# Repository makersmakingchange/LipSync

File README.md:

# LipSync

The LipSync is a mouth-operated sip-and-puff joystick that can emulate a mouse, wireless Bluetooth mouse, or gamepad. It enables people with disabilities that limit their mobility to control a computer, gaming console, smart phone, or tablet.

This most recent version, the LipSync 4.1, is made up of the LipSync Joystick and LipSync Hub. The Joystick is the primary user interface, and contains a low-force Hall-Effect joystick and sip and puff sensors. The Hub has a display that provides a graphical interface for independently adjusting settings, as well as it provides the connection to the host device and up to three external assistive switches with 3.5 mm jacks.

The device is comprised of off-the-shelf electronics and hardware, a custom PCB and 3D printed parts. The overall cost of materials (including materials required in bulk) for a single build is about $325 (plus shipping). In larger quantities, the cost of materials is closer to $175.

The LipSync is compatible with a range of host devices that are able to support a USB Mouse, a USB Gamepad and/or a Bluetooth Mouse. Compatible devices include PC and Mac computers and laptops, Android, iOS, and Windows smartphone and tablets, and the Xbox Adaptive Controller. 

The LipSync is Open Assistive Technology (OpenAT) and is certified as Open Source Hardware by the Open Source Hardware Association under the OSHWA UID [CA000046](https://certification.oshwa.org/ca000046.html). Under the terms of the open source hardware licenses, the LipSync may be built, used, and improved by anyone.  

Older versions of the LipSync are now obsolete. Documentation and design files are still available at the [LipSync Classic Repository.](https://github.com/makersmakingchange/OldLipSync)

The existing LipSync Interface Cable options in the BOM are not in stock. We are working on sourcing suitable alternatives.

Last updated: 2025-Jul-22

Makers Making Change Assistive Device Library Listing: [https://www.makersmakingchange.com/s/product/LipSync](https://www.makersmakingchange.com/s/product/lipsync/01tJR000000698fYAA)

## OpenAT Joysticks
This design is part of the [OpenAT Joystick Project](https://github.com/makersmakingchange/OpenAT-Joysticks), a collection of open source designs for digital access and adapted gaming. 

## How to Obtain the Device
### 1. Do-it-Yourself (DIY) or Do-it-Together (DIT)

This is an open-source assistive technology, so anyone is free to build it. All of the files and instructions required to build the device are contained within this repository. Refer to the Maker Guide below.

### 2. Request a build of this device

You may also submit a build request through the [MMC Library Page](https://www.makersmakingchange.com/s/product/LipSync/<mmc-salesforce-id>) to have a volunteer maker build the device. As the requestor, you are responsible for reimbursing the maker for the cost of materials and any shipping.

### 3. Build this device for someone else

If you have the skills and equipment to build this device, and would like to donate your time to create the device for someone who needs it, visit the [MMC Maker Wanted](https://makersmakingchange.com/maker-wanted/) section.

## Build Instructions

### 1. Read through the Maker Guide

The [Maker Guide](/Documentation/LipSync_Maker_Guide.pdf) contains all the necessary information to build this device, including tool lists, assembly instructions, programming instructions and testing instructions.

### 2. Order the Off-The-Shelf Components

The [Bill of Materials](/Documentation/LipSync_BOM.csv) lists all of the parts and components required to build the device. 

### 3. Print the 3D Printable components

All of the files and individual print files can be in the [/Build_Files/3D_Printing_Files](/Build_Files/3D_Printing_Files/) folder.

### 4. Assemble the LipSync

Reference the Assembly Guide section of the [Maker Guide](/Documentation/LipSync_Maker_Guide.pdf) for the tools and steps required to build each portion.

## How to improve this Device
As open source assistive technology, you are welcomed and encouraged to improve upon the design. 

## Files
### Documentation
| Document             | Version | Link                                                                     | Notes             |
|----------------------|---------|--------------------------------------------------------------------------|-------------------|
| Design Rationale     | 4.1     | [LipSync_Design_Rationale](/Documentation/LipSync_Design_Rationale.pdf)  |                   |
| Maker Guide          | 4.1     | [LipSync_Maker_Guide](/Documentation/LipSync_Maker_Guide.pdf)            |                   |
| Bill of Materials    | 4.1     | [LipSync_Bill_of_Materials](/Documentation/LipSync_BOM.csv)              |                   |
| User Guide           | 4.1     | [LipSync_User_Guide](/Documentation/LipSync_User_Guide.pdf)              |                   |
| Quickstart Guide     | 4.1     | [LipSync_Quickstart_Guide](/Documentation/LipSync_Quickstart_Guide.pdf)  |                   |
| Changelog            | 4.1     | [LipSync_Changelog](CHANGES.txt)                                         |                   |

### Design Files
 - [CAD Files](/Design_Files/CAD_Design_Files)
 - [PCB Files](/Design_Files/PCB_Design_Files)

### Build Files
 - [3D Printing Files](/Build_Files/3D_Printing_Files/)
 - [PCB Files](/Build_Files/PCB_Build_Files/)
 - [Firmware Files](/Build_Files/Firmware_Files)

## License
Copyright (c) 2024-2025 Neil Squire / Makers Making Change.

This repository describes Open Hardware:
 - Everything needed or used to design, make, test, or prepare the LipSync is licensed under the [CERN 2.0 Weakly Reciprocal license (CERN-OHL-W v2) or later](https://cern.ch/cern-ohl ) .
 - All software is under the [GNU General Public License v3.0 (GPL-3.0)](https://www.gnu.org/licenses/gpl.html).
 - Accompanying material such as instruction manuals, videos, and other copyrightable works that are useful but not necessary to design, make, test, or prepare the LipSync are published under a [Creative Commons Attribution-ShareAlike 4.0 license (CC BY-SA 4.0)](https://creativecommons.org/licenses/by-sa/4.0/) .

You may redistribute and modify this documentation and make products using it under the terms of the [CERN-OHL-W v2](https://cern.ch/cern-ohl).
This documentation is distributed WITHOUT ANY EXPRESS OR IMPLIED WARRANTY, INCLUDING OF MERCHANTABILITY, SATISFACTORY QUALITY AND FITNESS FOR A PARTICULAR PURPOSE.
Please see the CERN-OHL-W v2 for applicable conditions.

Source Location: https://github.com/makersmakingchange/LipSync

## Attribution

The LipSync was designed by Neil Squire Society / Makers Making Change. The initial development of a 3D printable LipSync was supported by the Google Impact Challenge: Disabilities grant from Google.org. Further development was supported through the Government of Canada's Innovation Science and Economic Development [Accessible Technology Program](https://ised-isde.canada.ca/site/accessible-technology-program). These and other funders have also enabled Neil Squire / Makers Making Change to deploy numerous LipSyncs to users at reduced cost.

The latest design (V4.0) incorporates feedback and suggestions from numerous users, clinicians, and volunteer makers. In particular, 4.0.AlphaII was tested by the following users: Omar Al-azawi, Don Danbrook, Ean Price, Jim Ryan and Kaileen Selig.

V4.0 incorporates several commercially available open source hardware components:
 - [Adafruit TLV493D Triple-Axis Magnetometer - STEMMA QT / Qwiic](https://www.adafruit.com/product/4366). The PCB design is available under a CC-BY-SA 3.0 license at https://github.com/adafruit/Adafruit-TLV493D-PCB. 
 - [Adafruit LPS33HW Water Resistant Pressure Sensor - STEMMA QT](https://www.adafruit.com/product/4414). The PCB design is available under a CC-BY-SA 3.0 license at https://github.com/adafruit/Adafruit-LPS3X-PCB. 
 - [Adafruit LPS22 Pressure Sensor - STEMMA QT / Qwiic - LPS22HB](https://www.adafruit.com/product/4633). The PCB design is available under a CC-BY-SA 3.0 license at https://github.com/adafruit/Adafruit-LPS2X-PCB. 
 - [Adafruit 128X64 monochrome OLED Display Board](https://www.adafruit.com/product/938). The PCB design is available under a CC-BY-SA 3.0 license at https://github.com/adafruit/Adafruit-128x64-Monochrome-OLED-PCB.
 - [SparkFun Qwiic Adapter Board (DEV-14495)](https://www.sparkfun.com/products/14495). The PCB design is available under a CC-BY-SA 4.0 license at https://github.com/sparkfun/Qwiic_Adapter.   
 - [SparkFun RJ11 Breakout Board (BOB-14021)](https://www.sparkfun.com/products/14021). The PCB design is available under a CC-BY-SA 3.0 license at https://github.com/sparkfun/RJ11_Breakout. 

The LipSync firmware utilizes the Arduino development platform, an open-source electronics platform based on easy-to-use hardware and software. Arduino is developed and maintained by the Arduino community, and the project wouldn't be possible without their contributions.
Arduino is a registered trademark of Arduino AG. For more information about Arduino and to contribute to the community, visit the official Arduino website at www.arduino.cc.
The LipSync Firmware code uses several libraries:
 - [Adafruit_BusIO](https://github.com/adafruit/Adafruit_BusIO)  by Adafruit
 - [Adafruit_GFX](https://github.com/adafruit/Adafruit-GFX-Library) by Adafruit
 - [Adafruit_LPS2X](https://github.com/adafruit/Adafruit_LPS2X) by Adafruit
 - [Adafruit_LPS33HW](https://github.com/adafruit/Adafruit_LPS35HW) by Adafruit
 - [Adafruit_Sensor](https://github.com/adafruit/Adafruit_Sensor) by Adafruit
 - [Adafruit_SSD1306](https://github.com/adafruit/Adafruit_SSD1306) by Adafruit
 - [ArduinoJson](https://github.com/bblanchon/ArduinoJson) by Benoit Blanchon
 - [TLV493D-A1B6](https://github.com/Infineon/TLV493D-A1B6-3DMagnetic-Sensor) by Infineon Technologies

### Contributors
Designers:
 
 - Derrick Andrews, Neil Squire Society / Makers Making Change.
 - Stephan Dobri, Neil Squire Society / Makers Making Change.
 - Tyler Fentie, Neil Squire Society / Makers Making Change.
 - Milad Hajihassan, Neil Squire Society / Makers Making Change.
 - Jake McIvor, Neil Squire Society / Makers Making Change.
 - Stephen Moyer, Neil Squire Society / Makers Making Change.
 - Brad Wellington, Neil Squire Society / Makers Making Change.
 - Josie Versloot, Neil Squire Society / Makers Making Change.
 
## Open Source Hardware Certification

The LipSync has been certified as open source hardware by the Open Source Hardware Association under the OSHWA UID [CA000046](https://certification.oshwa.org/ca000046.html).

---

<!-- ABOUT MMC START -->
## About Makers Making Change

Makers Making Change is a program of [Neil Squire](https://www.neilsquire.ca/), a Canadian non-profit that uses technology, knowledge, and passion to empower people with disabilities.

Makers Making Change leverages the capacity of community based Makers, Disability Professionals and Volunteers to develop and deliver affordable Open Source Assistive Technologies.

 - Website: [www.MakersMakingChange.com](https://www.makersmakingchange.com/)
 - GitHub: [makersmakingchange](https://github.com/makersmakingchange)
 - Bluesky: [@makersmakingchange.bsky.social](https://bsky.app/profile/makersmakingchange.bsky.social)
 - Instagram: [@makersmakingchange](https://www.instagram.com/makersmakingchange)
 - Facebook: [makersmakechange](https://www.facebook.com/makersmakechange)
 - LinkedIn: [Neil Squire Society](https://www.linkedin.com/company/neil-squire-society/)
 - Thingiverse: [makersmakingchange](https://www.thingiverse.com/makersmakingchange/about)
 - Printables: [MakersMakingChange](https://www.printables.com/@MakersMakingChange)

### Contact Us
For technical questions, to get involved, or to share your experience we encourage you to [visit our website](https://www.makersmakingchange.com/) or [contact us](https://www.makersmakingchange.com/s/contact).
<!-- ABOUT MMC END -->

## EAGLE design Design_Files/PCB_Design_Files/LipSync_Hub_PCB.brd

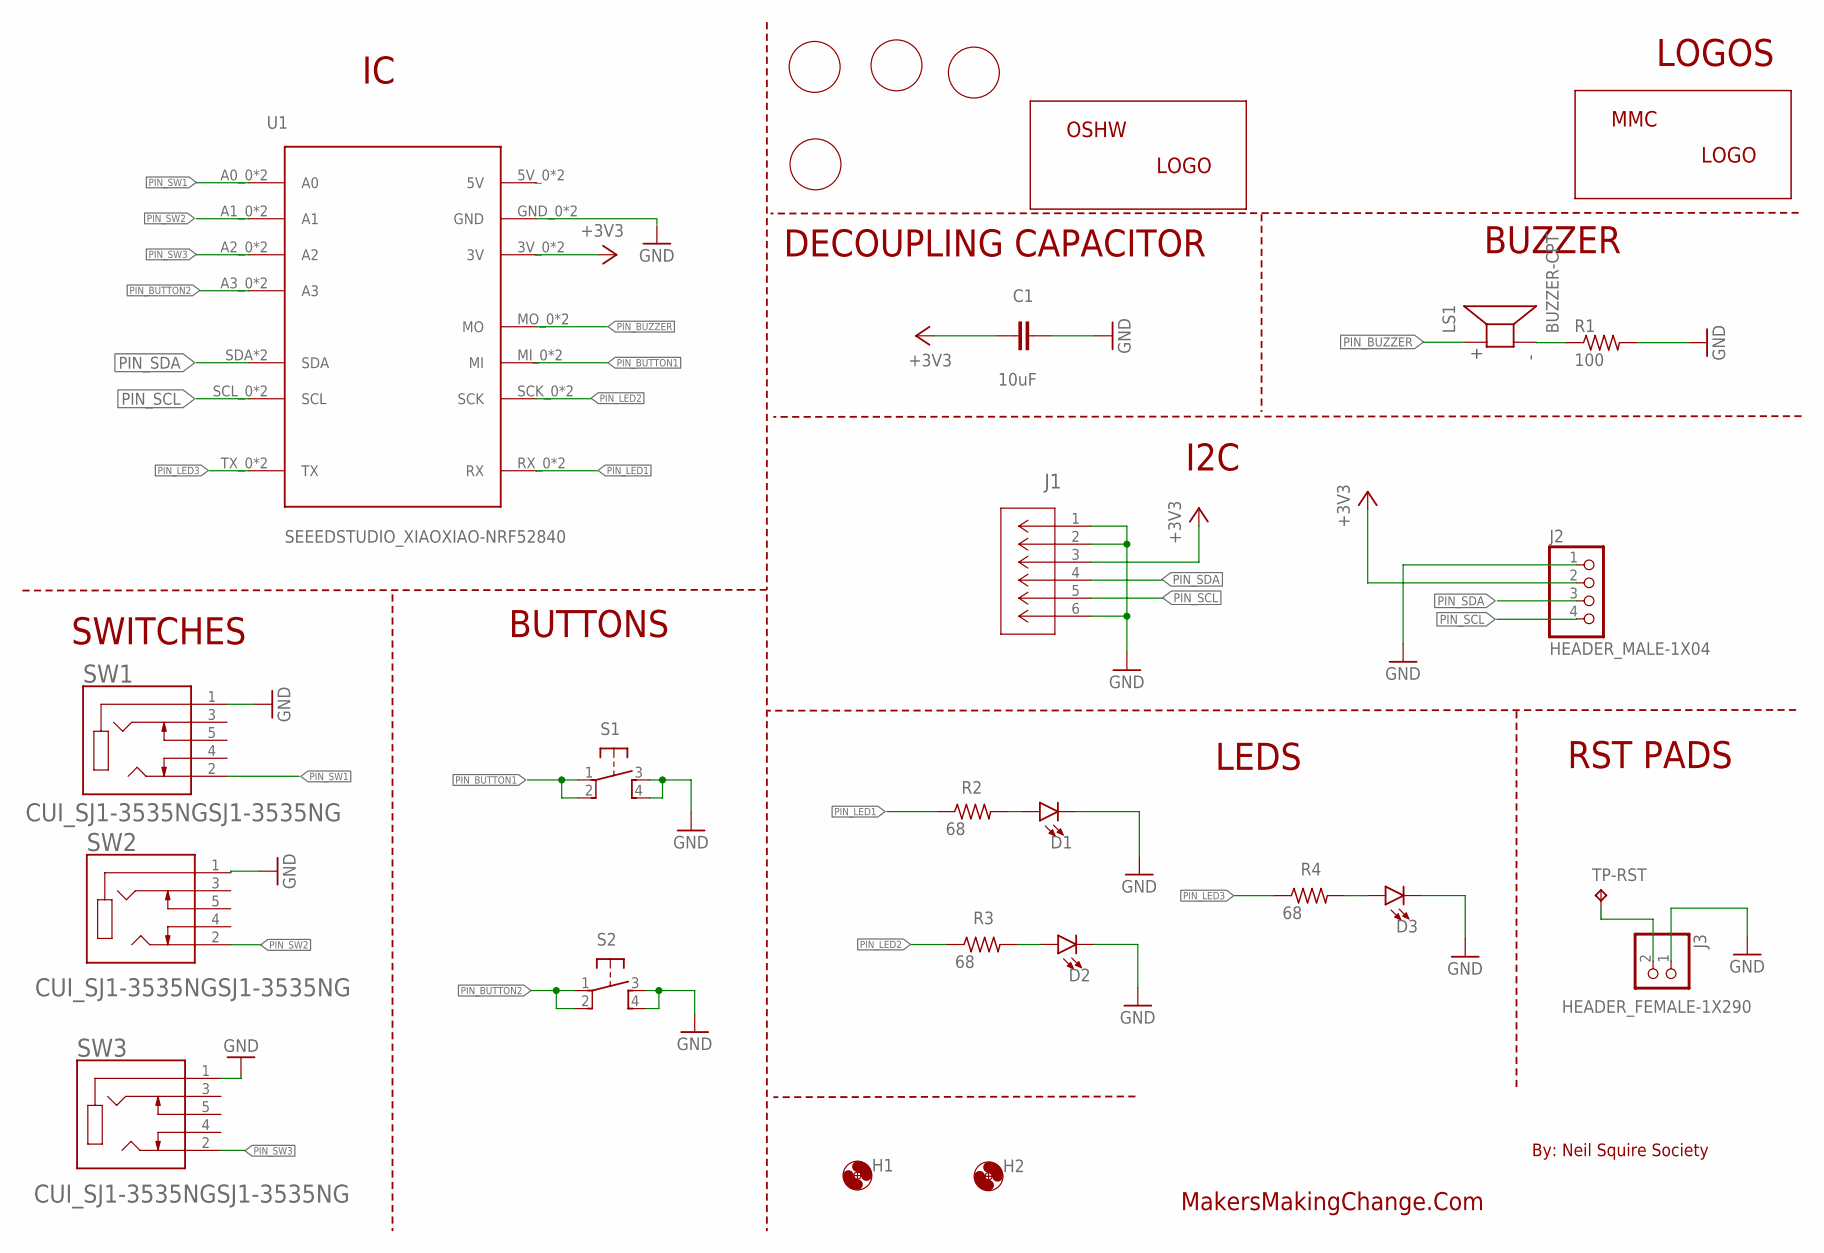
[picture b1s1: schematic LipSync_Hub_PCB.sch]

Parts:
C1: 10uF; CAP-050-030X075
D1, D2, D3: LED_5MM-5MM-RED-LONG; LED_5MM_RED_LONG
H1, H2: MOUNT-HOLE-3MM-CLEAR; HOLE-3MM-CLEAR
J1: 5555165-1; CONN6_5555165-1
J2: HEADER_MALE-1X04
J3: HEADER_FEMALE-1X290; HEADER_FEMALE-1X02_90
LOGO-BACK: MMC_LABEL-BACK; LABEL-BACK
LOGO-FRONT: MMC_LABEL-FRONT; LABEL-FRONT
LOGO-LIPSYNC-BACK: MMC_LABEL-LIPSYNC-X-LG; LABEL-LIPSYNC-X-LG
LOGO-MMC-BACK: MMC_LOGO-MD; MMC_MEDIUM_LOGO
LOGO-NORTH: MMC_LABEL-UP; LABEL-UP
LOGO-OSWH: OSHW_LOGO-SM; OSHW_SMALL_LOGO
LS1: BUZZER-CPT; CUI_CPT-1255C-090
R1: 100; RESISTOR_0205/7
R2, R3, R4: 68; RESISTOR_0205/7
S1, S2: SWITCH_OMRON-PTH-12; B3F-5050
SW1, SW2, SW3: CUI_SJ1-3535NGSJ1-3535NG; CUI_SJ1-3535NG
TP-RST: TESTPAD_TPB1,27; TESTPAD_B1,27
U1: SEEEDSTUDIO_XIAOXIAO-NRF52840; SEEEDSTUDIO_XIAO_NRF52840

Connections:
+3V3: C1.2, J1.3, J2.2, U1.3V_0 (3V), U1.3V_1 (3V)
GND: C1.1, D1.K (C), D2.K (C), D3.K (C), J1.1, J1.2, J1.6, J2.1, J3.1, R1.2, S1.3, S1.4, S2.3, S2.4, SW1.1, SW2.1, SW3.1, U1.GND_0 (GND), U1.GND_1 (GND)
unnamed: LS1.N, R1.1
unnamed: D2.A, R3.2
unnamed: J3.2, TP-RST.TP
unnamed: D3.A, R4.2
unnamed: D1.A, R2.2
PIN_BUTTON1: S1.1, S1.2, U1.MI_0 (MI), U1.MI_1 (MI)
PIN_BUTTON2: S2.1, S2.2, U1.A3_0 (A3), U1.A3_1 (A3)
PIN_BUZZER: LS1.P, U1.MO_0 (MO), U1.MO_1 (MO)
PIN_LED1: R2.1, U1.RX_0 (RX), U1.RX_1 (RX)
PIN_LED2: R3.1, U1.SCK_0 (SCK), U1.SCK_1 (SCK)
PIN_LED3: R4.1, U1.TX_0 (TX), U1.TX_1 (TX)
PIN_SCL: J1.5, J2.4, U1.SCL_0 (SCL), U1.SCL_1 (SCL)
PIN_SDA: J1.4, J2.3, U1.SDA, U1.SDA_0 (SDA)
PIN_SW1: SW1.2, U1.A0_0 (A0), U1.A0_1 (A0)
PIN_SW2: SW2.2, U1.A1_0 (A1), U1.A1_1 (A1)
PIN_SW3: SW3.2, U1.A2_0 (A2), U1.A2_1 (A2)

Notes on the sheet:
By: Neil Squire Society
MakersMakingChange.Com
SWITCHES
BUZZER
I2C
DECOUPLING CAPACITOR
LOGOS
BUTTONS
LEDS
RST PADS

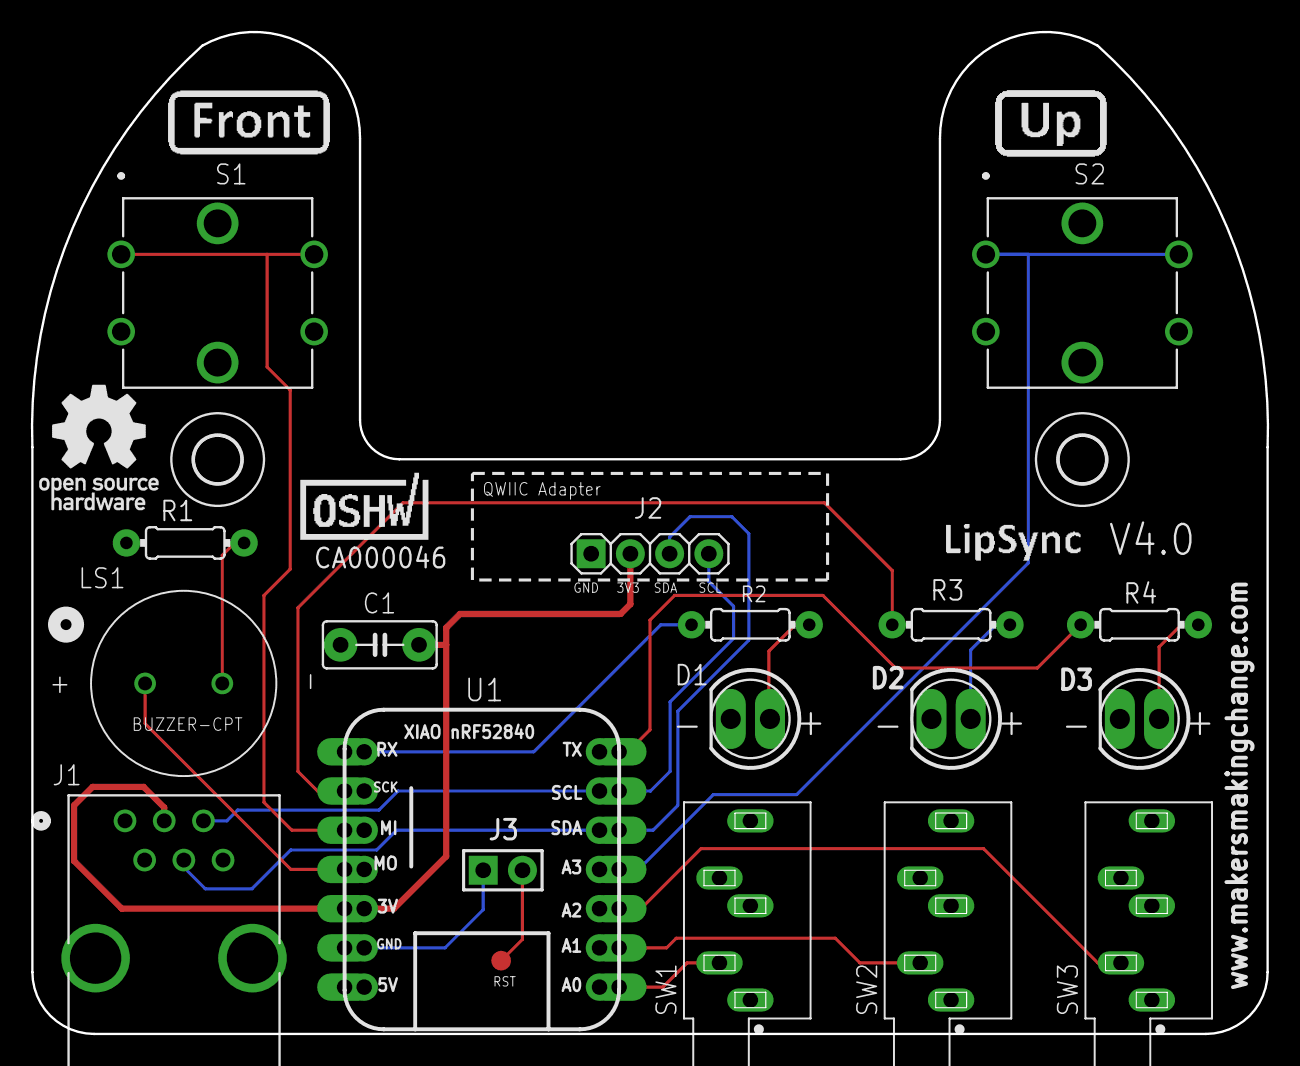
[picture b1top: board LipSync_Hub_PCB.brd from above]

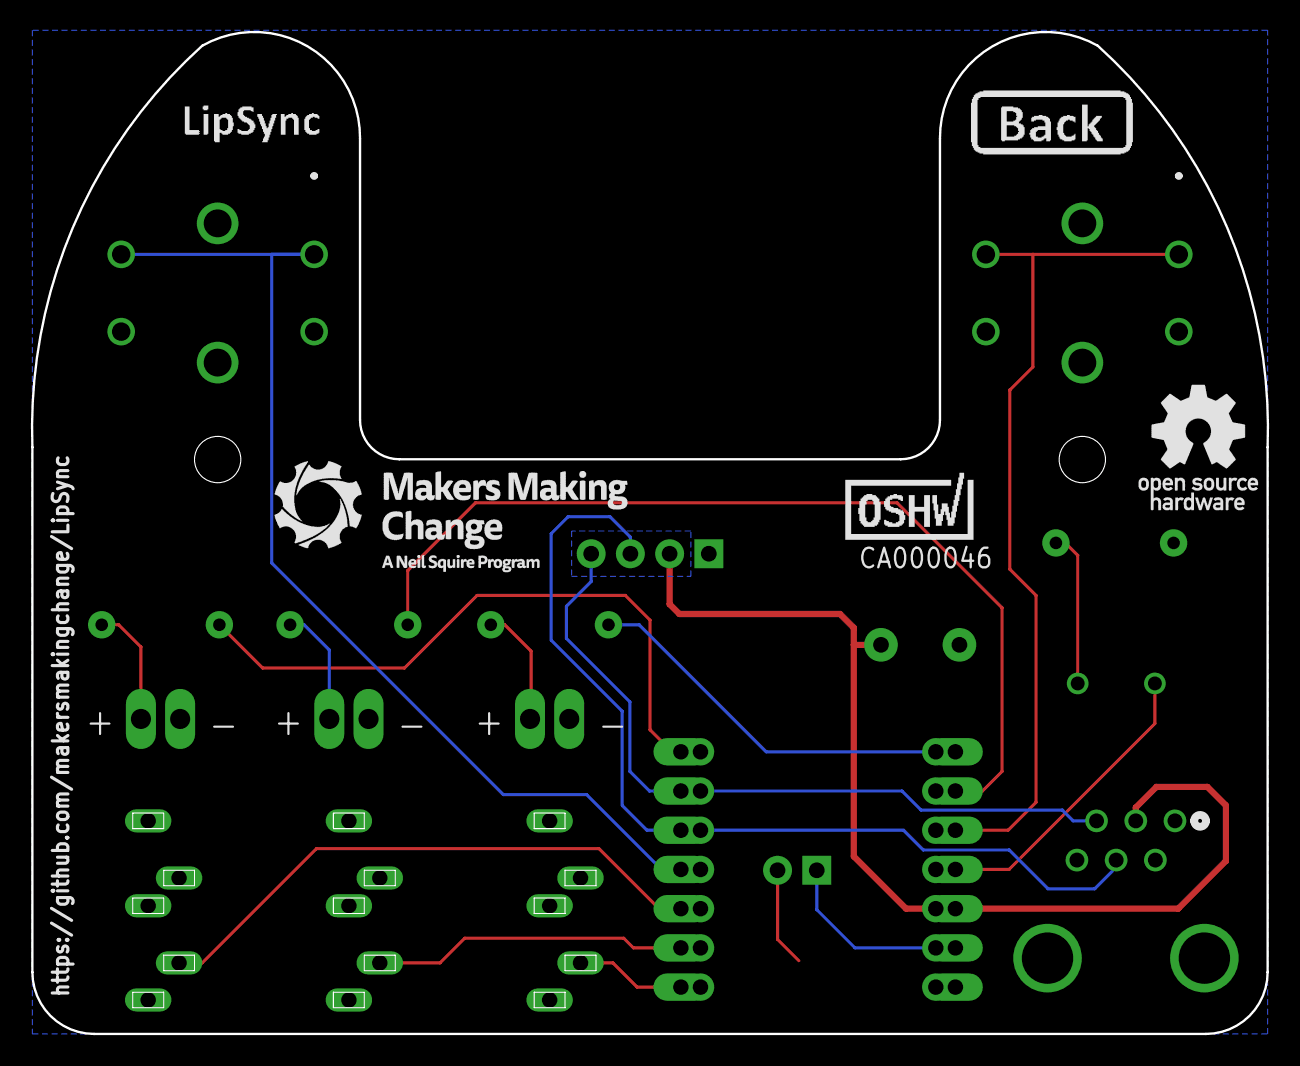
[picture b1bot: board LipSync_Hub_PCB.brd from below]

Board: 2 copper layers, 80.0 x 64.9 mm, 31 parts (5 on the bottom side), 18 nets.

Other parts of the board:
U$1: OSHW_SMALL_LOGO
U$2, U$4: CA000046; CERT-SMALL-SILK
U$3: LABEL-LIPSYNC-X-LG

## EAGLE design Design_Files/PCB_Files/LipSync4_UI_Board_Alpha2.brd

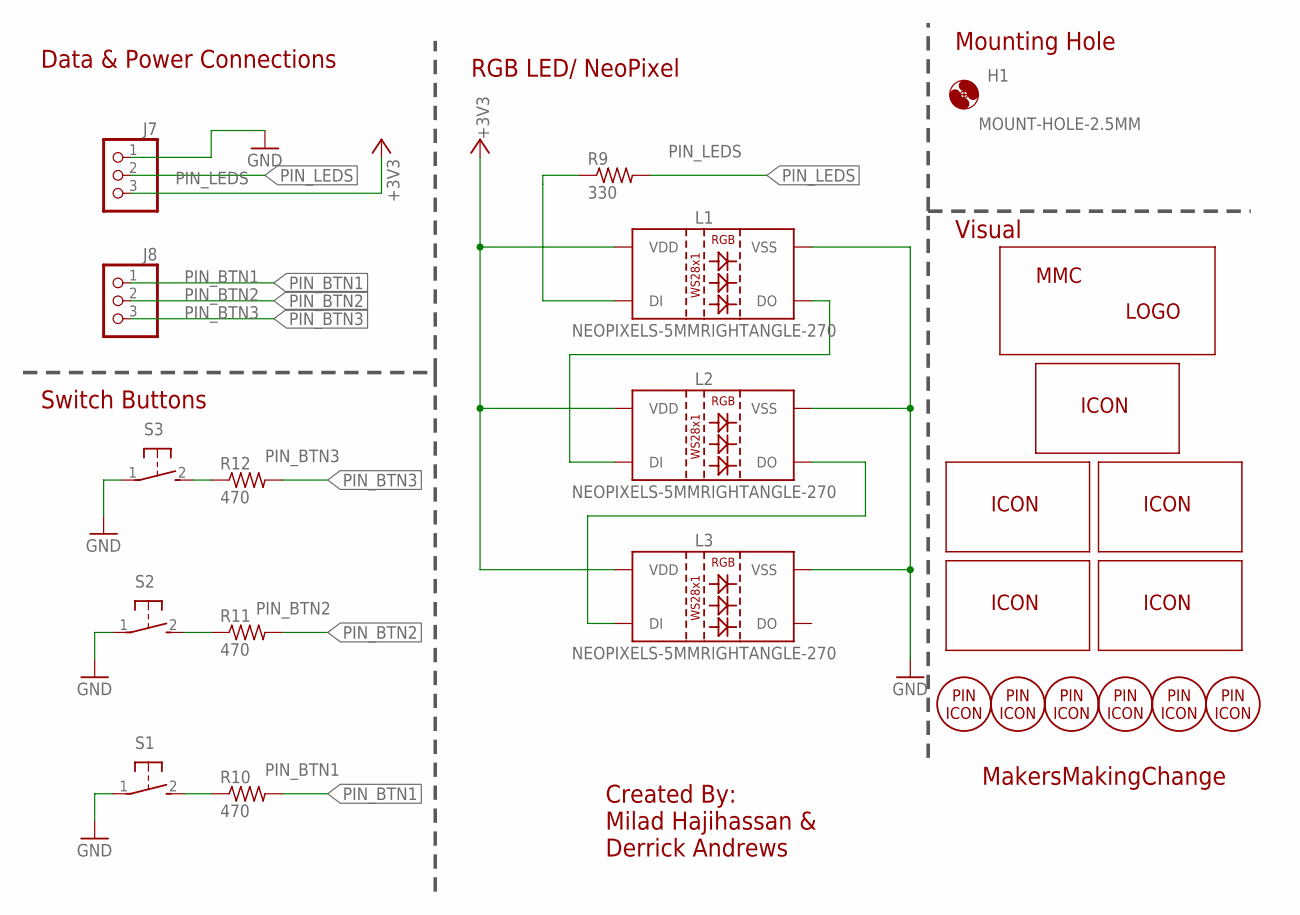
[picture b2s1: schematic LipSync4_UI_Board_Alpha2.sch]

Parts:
H1: MOUNT-HOLE-2.5MM; HOLE-2.5MM
J7, J8: HEADER_FEMALE-1X3-LONGER; HEADER_FEMALE-1X03_LONGER
L1, L2, L3: NEOPIXELS-5MMRIGHTANGLE-270; NEOPIXELS-RIGHTANGLE-270-5MM
LABEL_ALPHA2-BOTTOM: MMC_ICON-ALPHA2; ICON_ALPHA2
LABEL_BUTTON: MMC_ICON-BUTTON; ICON_BUTTON
LABEL_ICON_PIN1: MMC_PIN-ICON-PIN1; PIN-ICON_1
LABEL_ICON_PIN2: MMC_PIN-ICON-PIN2; PIN-ICON_2
LABEL_ICON_PIN3: MMC_PIN-ICON-PIN3; PIN-ICON_3
LABEL_ICON_PIN-DATA: MMC_PIN-ICON-DATA; PIN-ICON_DATA
LABEL_ICON_PIN-GND: MMC_PIN-ICON-GND; PIN-ICON_GND
LABEL_ICON_PIN-VCC: MMC_PIN-ICON-VCC; PIN-ICON_VCC
LABEL_LED: MMC_ICON-LED; ICON_LED
LABEL_LIPSYNC-BOTTOM: MMC_ICON-LIPSYNC4; ICON_LIPSYNC4
LABEL_MMC-LOGO: MMC_LOGO-SM; MMC_SMALL_LOGO
LABE_UI-BOARD-BOTTOM: MMC_ICON-UI-BOARD; ICON_UI-BOARD
R9: 330; RESISTOR_0204/5
R10, R11, R12: 470; RESISTOR_0204/5
S1, S2, S3: SWITCH_OMRON_RA-RA; B3F-31XX

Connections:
+3V3: J7.3, L1.P2 (VDD), L2.P2 (VDD), L3.P2 (VDD)
GND: J7.1, L1.P3 (VSS), L2.P3 (VSS), L3.P3 (VSS), S1.1, S2.1, S3.1
unnamed: R11.1, S2.2
unnamed: L1.P1 (DI), R9.1
unnamed: R10.1, S1.2
unnamed: L1.P4 (DO), L2.P1 (DI)
unnamed: R12.1, S3.2
unnamed: L2.P4 (DO), L3.P1 (DI)
PIN_BTN1: J8.1, R10.2
PIN_BTN2: J8.2, R11.2
PIN_BTN3: J8.3, R12.2
PIN_LEDS: J7.2, R9.2

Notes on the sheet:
Switch Buttons
MakersMakingChange
RGB LED/ NeoPixel
Data & Power Connections
Mounting Hole
Visual
Created By: Milad Hajihassan & Derrick Andrews

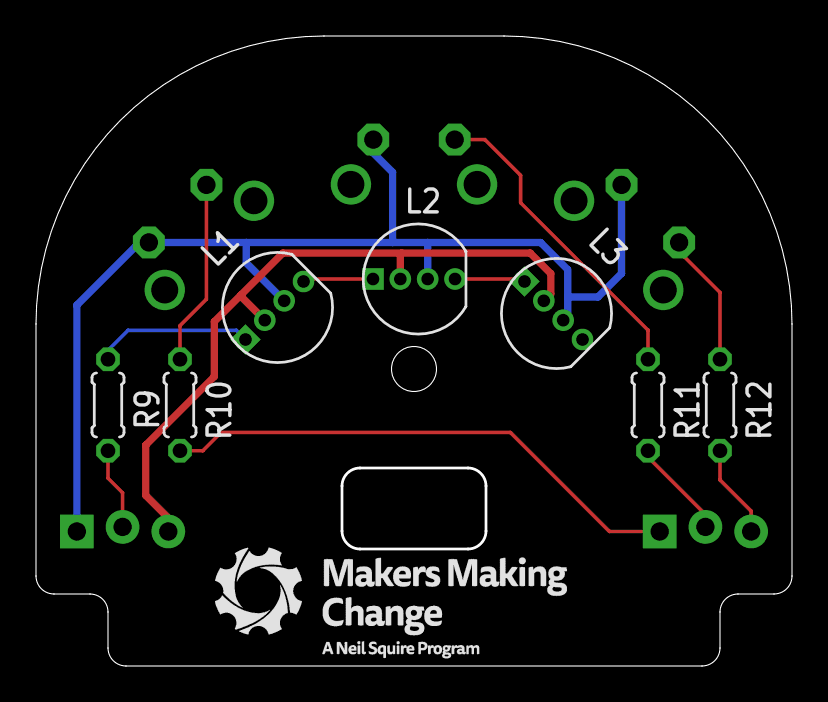
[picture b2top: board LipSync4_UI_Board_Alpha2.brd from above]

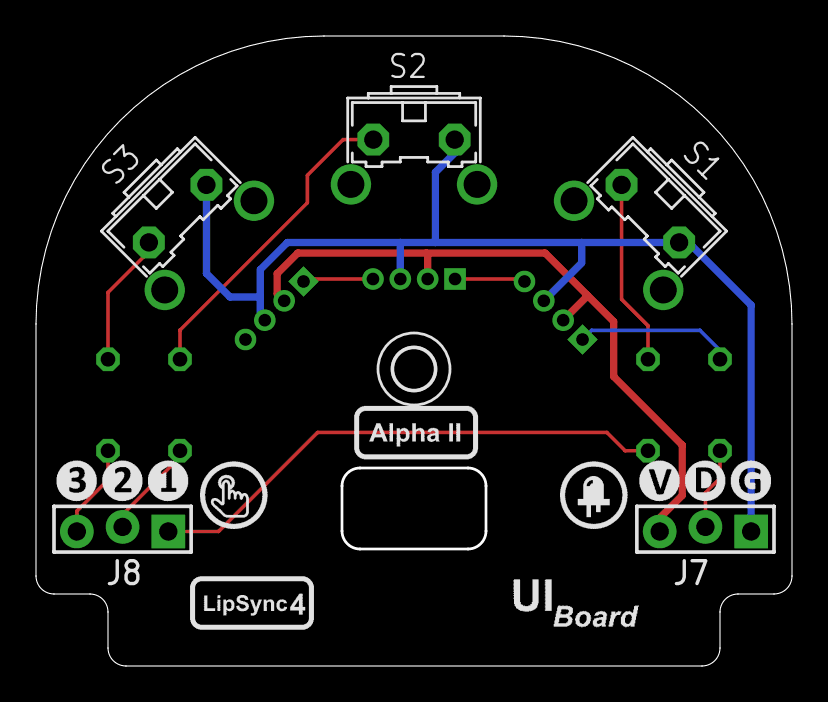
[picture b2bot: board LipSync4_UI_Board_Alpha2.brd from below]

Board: 2 copper layers, 42.0 x 35.0 mm, 25 parts (17 on the bottom side), 12 nets.

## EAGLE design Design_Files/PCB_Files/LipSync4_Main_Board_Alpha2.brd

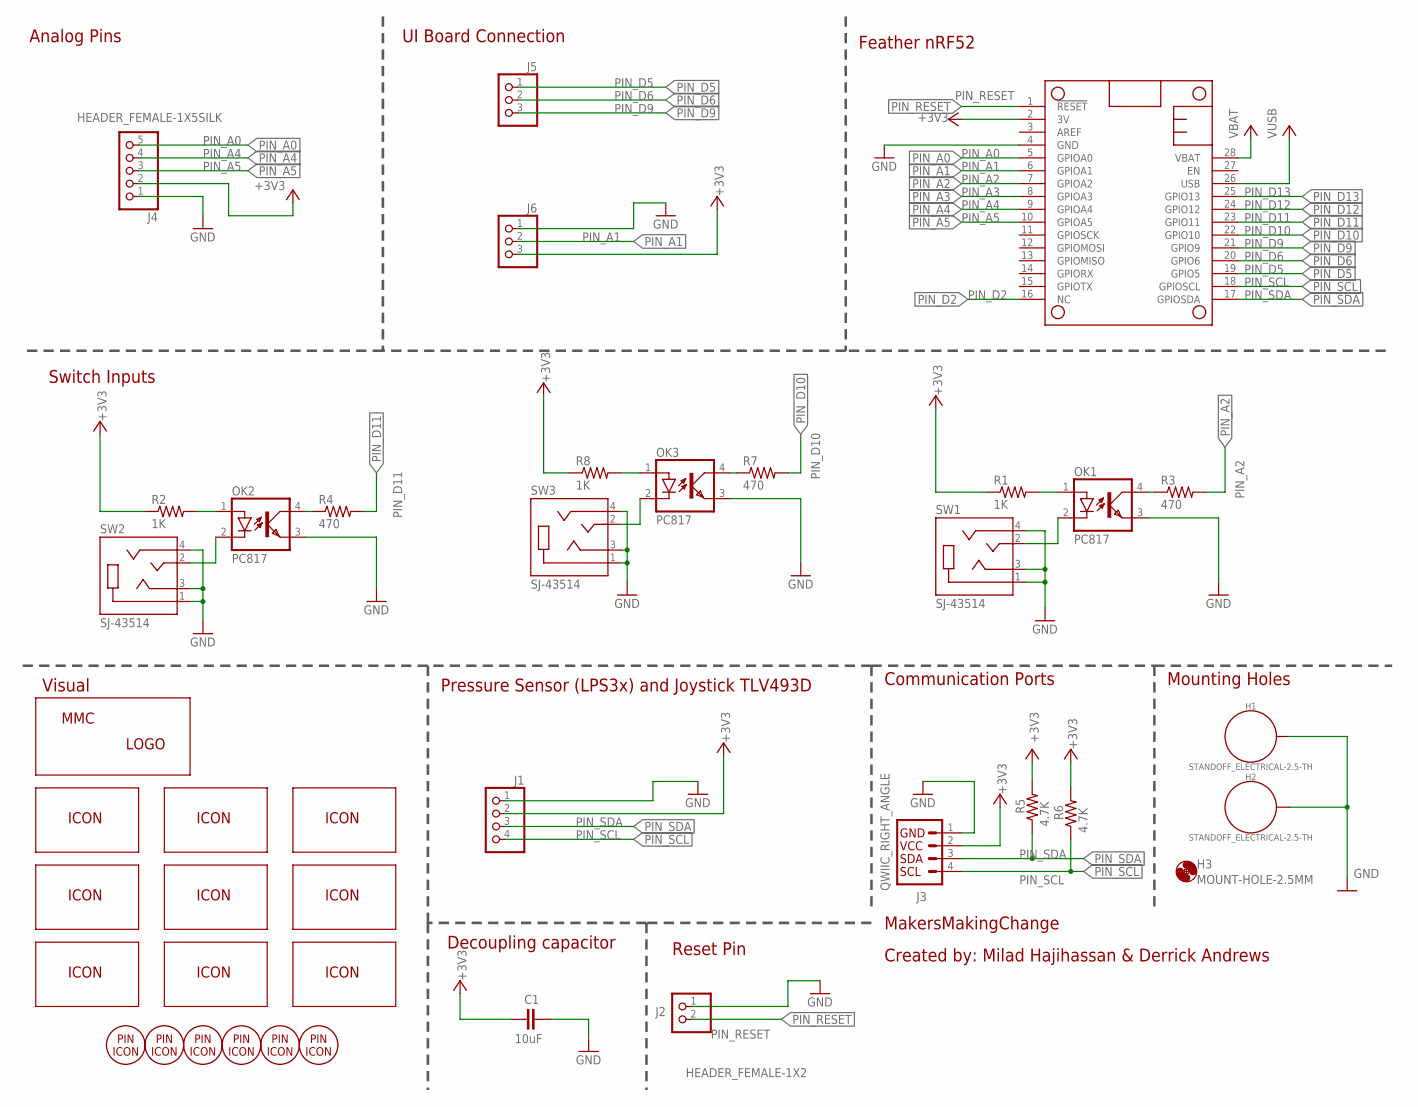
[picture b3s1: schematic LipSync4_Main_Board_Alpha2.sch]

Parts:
C1: 10uF; CAP-025-025X040
H1, H2: STANDOFF_ELECTRICAL-2.5-TH; STANDOFF-ELECTRICAL-2.5-TH
H3: MOUNT-HOLE-2.5MM; HOLE-2.5MM
J1: HEADER_FEMALE-1X4; HEADER_FEMALE-1X04
J2: HEADER_FEMALE-1X2; HEADER_FEMALE-1X02
J3: QWIIC_RIGHT_ANGLE; CONNECTORS_JST04_1MM_RA
J4: HEADER_FEMALE-1X5SILK; HEADER_FEMALE-1X05_SILK
J5, J6: HEADER_MALE-1X03/270; HEADER_MALE-1X03_LOCK/270
LABEL_ALPHA2: MMC_ICON-ALPHA2; ICON_ALPHA2
LABEL_I2C: MMC_ICON-I2C; ICON_I2C
LABEL_ICON_PIN1: MMC_PIN-ICON-PIN1; PIN-ICON_1
LABEL_ICON_PIN2: MMC_PIN-ICON-PIN2; PIN-ICON_2
LABEL_ICON_PIN3: MMC_PIN-ICON-PIN3; PIN-ICON_3
LABEL_ICON_PIN-DATA: MMC_PIN-ICON-DATA; PIN-ICON_DATA
LABEL_ICON_PIN-GND: MMC_PIN-ICON-GND; PIN-ICON_GND
LABEL_ICON_PIN-VCC: MMC_PIN-ICON-VCC; PIN-ICON_VCC
LABEL_LIPSYNC4: MMC_ICON-LIPSYNC4; ICON_LIPSYNC4
LABEL_MAIN-BOARD: MMC_ICON-MAIN-BOARD; ICON_MAIN-BOARD
LABEL_MMC: MMC_LOGO-SM; MMC_SMALL_LOGO
LABEL_RESET: MMC_ICON-RESET; ICON_RESET
LABEL_SPEAKER: MMC_ICON-SPEAKER; ICON_SPEAKER
LABEL_STEMMA: MMC_ICON-STEMMA; ICON_STEMMA
LABE_BUTTON: MMC_ICON-BUTTON; ICON_BUTTON
LABE_LED: MMC_ICON-LED; ICON_LED
OK1, OK2, OK3: PC817; DIL04
R1, R2, R8: 1K; RESISTOR_0204/5
R3, R4, R7: 470; RESISTOR_0204/5
R5, R6: 4.7K; RESISTOR_0204/5
SW1, SW2, SW3: SJ-43514; CUI_SJ-43514
U1: ADAFRUIT_FEATHER_NODIM; ADAFRUIT_FEATHERWING_DIM

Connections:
+3V3: C1.2, J1.2, J3.2, J4.2, J6.3, R1.1, R2.1, R5.2, R6.2, R8.1, U1.2 (3V)
GND: C1.1, H1.P1, H2.P1, J1.1, J2.1, J3.1, J4.1, J6.1, OK1.3 (EMIT), OK2.3 (EMIT), OK3.3 (EMIT), SW1.1 (SLEEVE), SW1.3 (RING1), SW1.4 (RING2), SW2.1 (SLEEVE), SW2.3 (RING1), SW2.4 (RING2), SW3.1 (SLEEVE), SW3.3 (RING1), SW3.4 (RING2), U1.4 (GND)
unnamed: OK3.1 (A), R8.2
unnamed: OK3.4 (COL), R7.1
unnamed: OK3.2 (C), SW3.2 (TIP)
unnamed: OK2.1 (A), R2.2
unnamed: OK2.4 (COL), R4.1
unnamed: OK1.1 (A), R1.2
unnamed: OK2.2 (C), SW2.2 (TIP)
unnamed: OK1.4 (COL), R3.1
unnamed: OK1.2 (C), SW1.2 (TIP)
PIN_A0: J4.5, U1.5 (GPIOA0)
PIN_A1: J6.2, U1.6 (GPIOA1)
PIN_A2: R3.2, U1.7 (GPIOA2)
PIN_A3: U1.8 (GPIOA3)
PIN_A4: J4.4, U1.9 (GPIOA4)
PIN_A5: J4.3, U1.10 (GPIOA5)
PIN_D2: U1.16 (NC)
PIN_D5: J5.1, U1.19 (GPIO5)
PIN_D6: J5.2, U1.20 (GPIO6)
PIN_D9: J5.3, U1.21 (GPIO9)
PIN_D10: R7.2, U1.22 (GPIO10)
PIN_D11: R4.2, U1.23 (GPIO11)
PIN_D12: U1.24 (GPIO12)
PIN_D13: U1.25 (GPIO13)
PIN_RESET: J2.2, U1.1 (!RESET)
PIN_SCL: J1.4, J3.4, R6.1, U1.18 (GPIOSCL)
PIN_SDA: J1.3, J3.3, R5.1, U1.17 (GPIOSDA)
VBAT: U1.28 (VBAT)
VUSB: U1.26 (USB)

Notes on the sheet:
Switch Inputs
Feather nRF52
MakersMakingChange
Communication Ports
Pressure Sensor (LPS3x) and Joystick TLV493D
UI Board Connection
Reset Pin
Analog Pins
Mounting Holes
Visual
Created by: Milad Hajihassan & Derrick Andrews
Decoupling capacitor

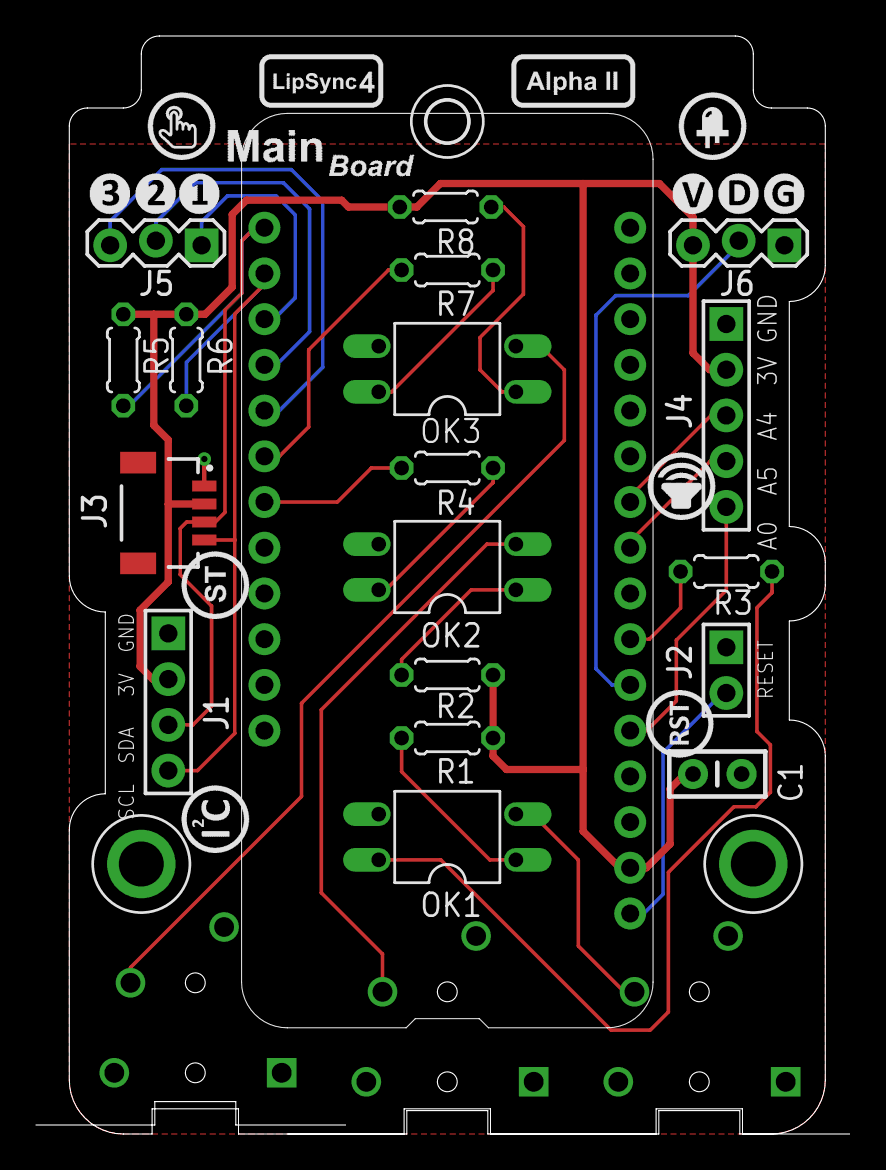
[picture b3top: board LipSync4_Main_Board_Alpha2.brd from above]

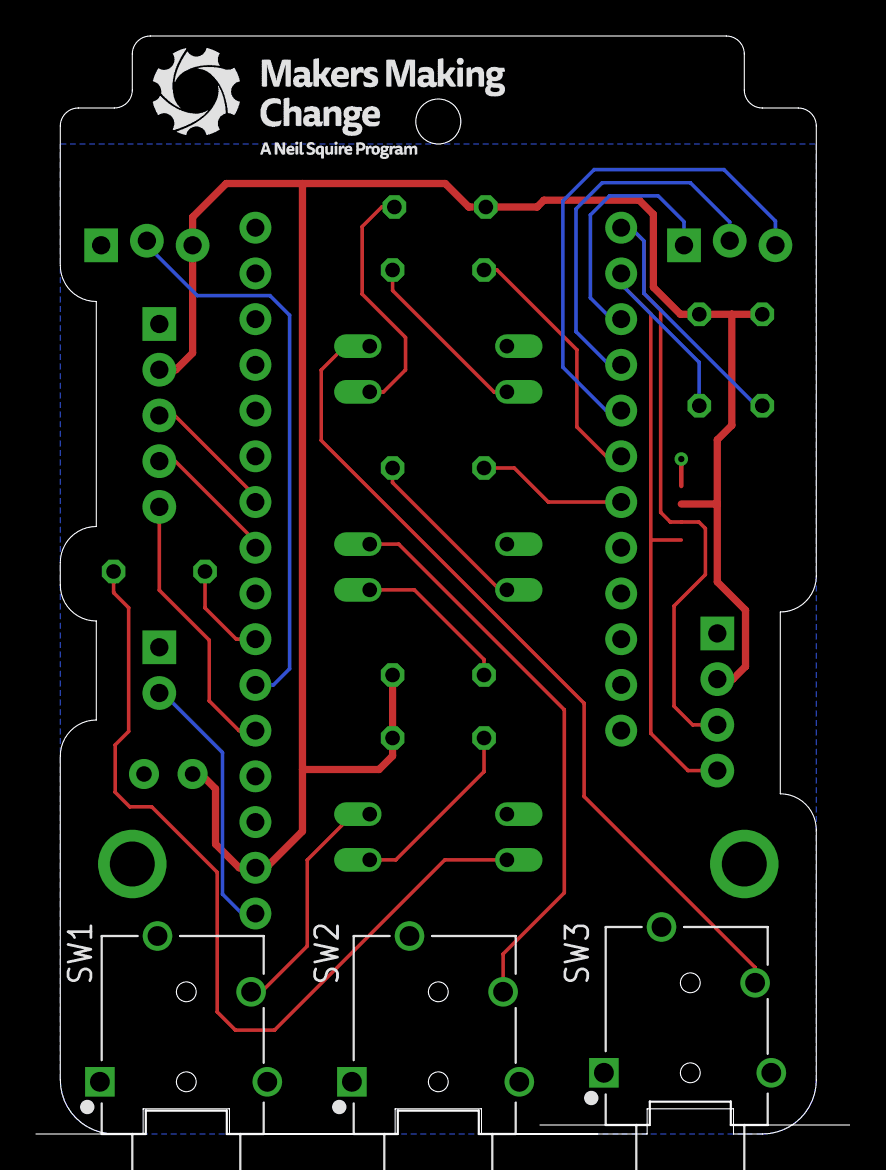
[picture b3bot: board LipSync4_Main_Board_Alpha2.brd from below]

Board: 2 copper layers, 45.2 x 61.0 mm, 41 parts (4 on the bottom side), 24 nets.

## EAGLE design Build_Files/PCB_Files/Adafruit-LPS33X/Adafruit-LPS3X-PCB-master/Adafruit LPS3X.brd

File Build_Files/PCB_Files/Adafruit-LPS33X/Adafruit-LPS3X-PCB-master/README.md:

# Adafruit-LPS35X-PCB
PCB files for the Adafruit LPS35HW and LPS33HW Breakouts

Format is EagleCAD schematic and board layout

For more details, check out the product page at

   * https://www.adafruit.com/product/4258
   * https://www.adafruit.com/product/4414

Adafruit invests time and resources providing this open source design, 
please support Adafruit and open-source hardware by purchasing 
products from Adafruit!

Designed by Adafruit Industries.  
Creative Commons Attribution, Share-Alike license, check license.txt for more information
All text above must be included in any redistribution

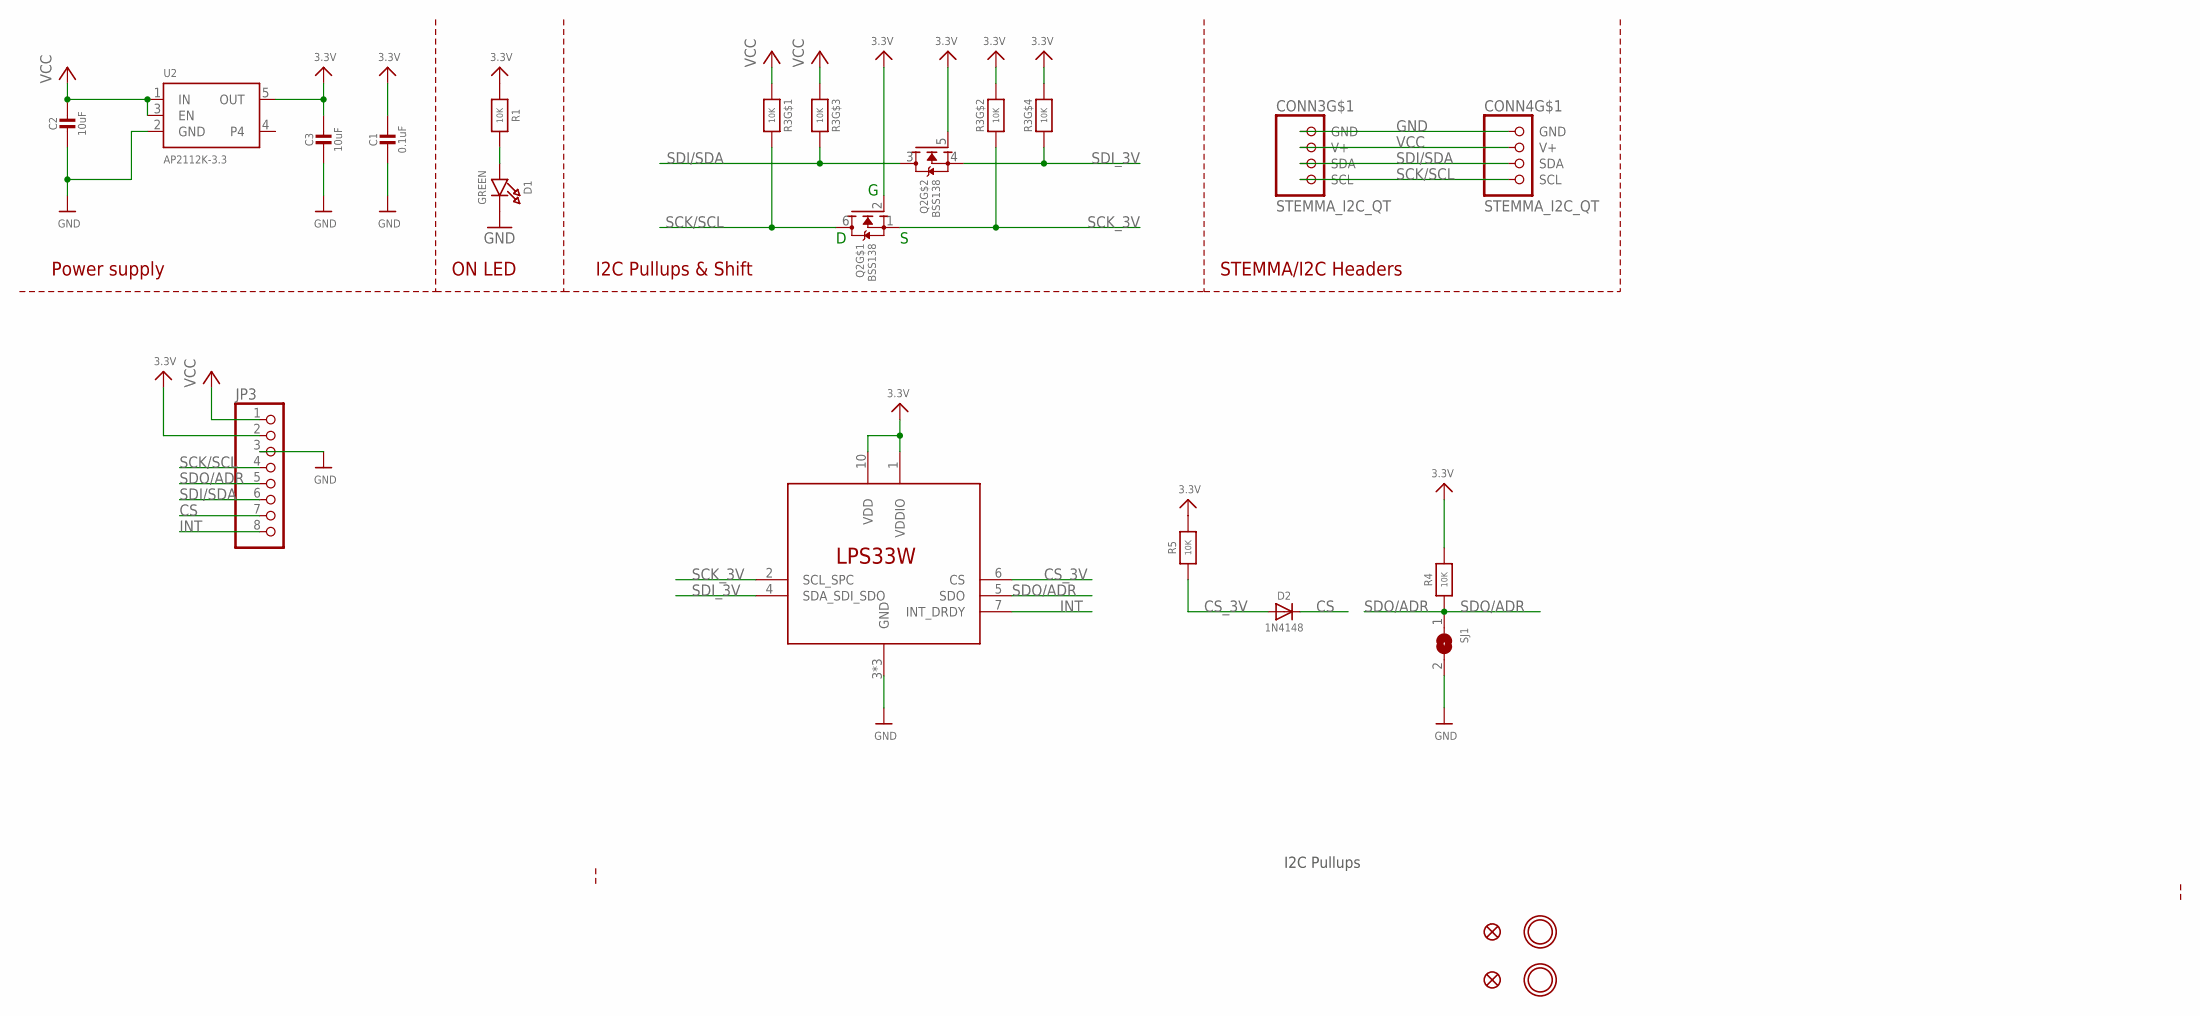
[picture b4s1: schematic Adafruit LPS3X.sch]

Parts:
C1: 0.1uF; 0603-NO
C2, C3: 10uF; 0805-NO
CONN3, CONN4: STEMMA_I2C_QT; JST_SH4
D1: GREEN; CHIPLED_0603_NOOUTLINE
D2: 1N4148; SOD-323
FID3, FID4: FIDUCIAL_1MM
JP3: HEADER-1X8ROUND; 1X08_ROUND
Q2: BSS138; SOT363
R1, R4, R5: 10K; 0603-NO
R3: 10K; RESPACK_4X0603
SJ1: SOLDERJUMPER; SOLDERJUMPER_ARROW_NOPASTE
U2: AP2112K-3.3; SOT23-5
U$1, U$17: MOUNTINGHOLE2.5; MOUNTINGHOLE_2.5_PLATED
U$2: LPS33W; CCLGA10L

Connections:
3.3V: C1.1, C3.1, JP3.2, Q2.2 (G), Q2.5 (G), R1.1, R3.2 (1), R3.4 (1), R4.2, R5.2, U2.5 (OUT), U$2.1 (VDDIO), U$2.10 (VDD)
CS: D2.C, JP3.7
CS_3V: D2.A, R5.1, U$2.6 (CS)
GND: C1.2, C2.2, C3.2, CONN3.1 (GND), CONN4.1 (GND), D1.C, JP3.3, SJ1.2, U2.2 (GND), U$2.3 (GND), U$2.8 (GND), U$2.9 (GND)
INT: JP3.8, U$2.7 (INT_DRDY)
unnamed: D1.A, R1.2
SCK/SCL: CONN3.4 (SCL), CONN4.4 (SCL), JP3.4, Q2.6 (D), R3.8 (2)
SCK_3V: Q2.1 (S), R3.7 (2), U$2.2 (SCL_SPC)
SDI/SDA: CONN3.3 (SDA), CONN4.3 (SDA), JP3.6, Q2.3 (D), R3.6 (2)
SDI_3V: Q2.4 (S), R3.5 (2), U$2.4 (SDA_SDI_SDO)
SDO/ADR: JP3.5, R4.1, SJ1.1, U$2.5 (SDO)
VCC: C2.1, CONN3.2 (V+), CONN4.2 (V+), JP3.1, R3.1, R3.3 (1), U2.1 (IN), U2.3 (EN)

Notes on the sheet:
I2C Pullups & Shift
STEMMA/I2C Headers
ON LED
Power supply
I2C Pullups

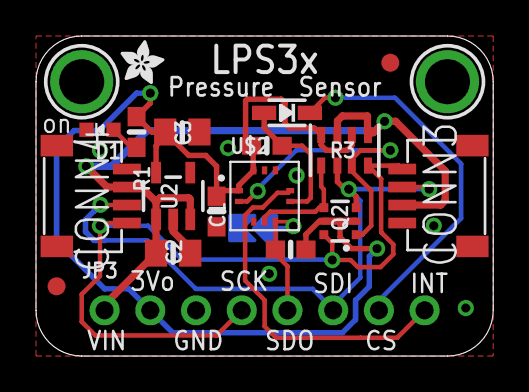
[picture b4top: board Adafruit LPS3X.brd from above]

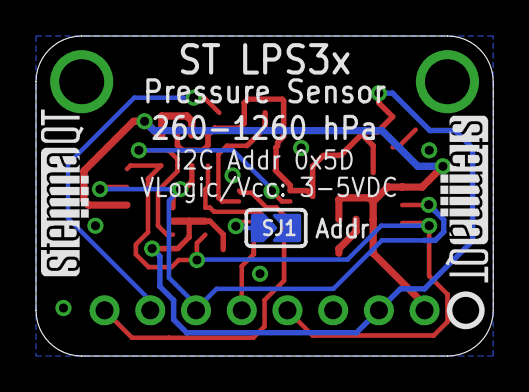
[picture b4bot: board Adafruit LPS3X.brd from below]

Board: 2 copper layers, 25.4 x 17.8 mm, 24 parts (4 on the bottom side), 12 nets.

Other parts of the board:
U$4: ADAFRUIT_2.5MM
U$25: PCBFEAT-REV-040
U$30, U$31: STEMMAQT

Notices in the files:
README.md:
List of open source licenses. Hardware: CERN-OHL-W-2.0, Software: GPL-3.0-or-later, Documentation: CC-BY-SA-4.0.
parts and their libraries:
microbuilder: This work is placed in the public domain, and may be freely used for commercial and non-commercial work with the following conditions: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
COPYRIGHT: Copyright (C) 2023 Ultra Librarian. All rights reserved.
